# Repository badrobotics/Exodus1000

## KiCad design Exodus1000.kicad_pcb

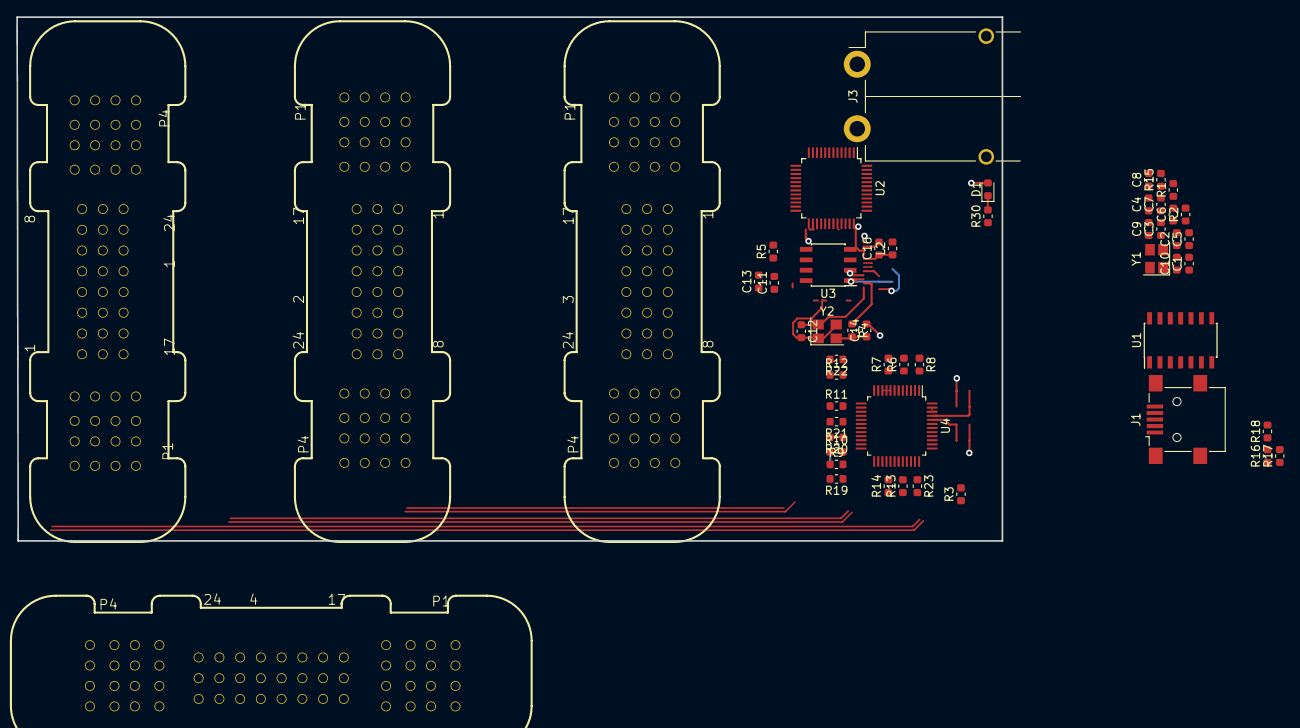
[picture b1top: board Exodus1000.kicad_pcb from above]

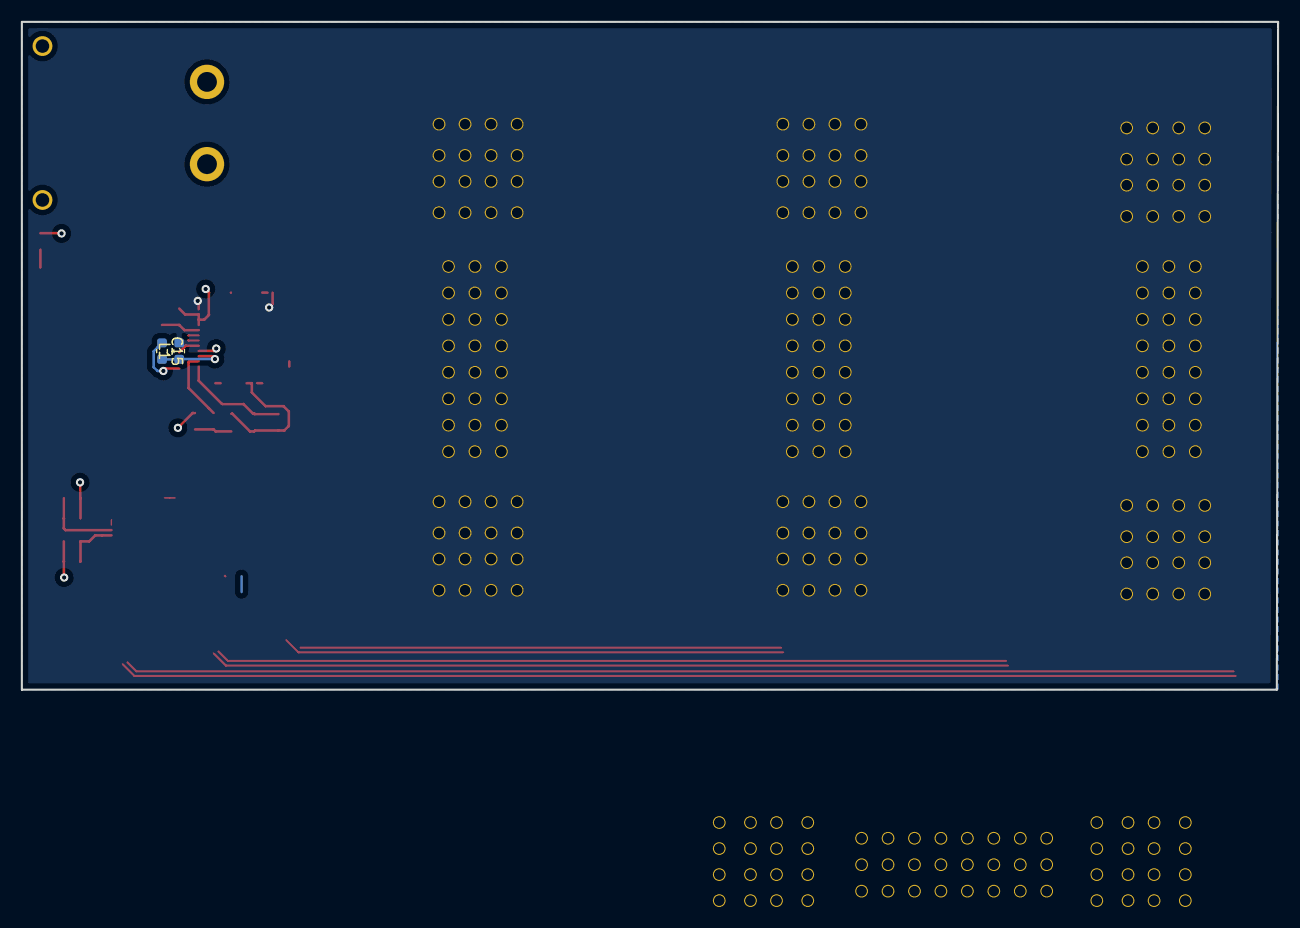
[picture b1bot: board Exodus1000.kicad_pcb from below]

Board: 4 copper layers, 120.7 x 64.1 mm, 55 parts (2 on the bottom side), 54 nets.

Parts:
1, 2, 3, 4: ET60S-02-24-02-X-VP-GP
C1, C2, C3, C4, C5, C6, C7, C8, C9, C10, C11, C12, C13, C14, C15, C16: C_Small; C_0603_1608Metric
D1: LED; LED_0603_1608Metric
J1: USB_B_Mini; USB_Mini-B_Lumberg_2486_01_Horizontal
J3: Conn_01x02; Anderson_PP15_1x2_RightAngle
L1, L2: Ferrite_Bead_Small; L_0603_1608Metric
R1, R2, R3, R4, R5, R6, R7, R8, R9, R10, R11, R12, R13, R14, R15, R16, R17, R18, R19, R20, R21, R22, R23, R30: R_Small; R_0603_1608Metric
U1: 74LS125; SOIC-14_3.9x8.7mm_P1.27mm
U2: tusb2077a; TQFP-48_7x7mm_P0.5mm
U3: 93LCxxB; SOIC-8_3.9x4.9mm_P1.27mm
U4: FT232H; LQFP-48_7x7mm_P0.5mm
Y1: Crystal_GND24; Crystal_SMD_SeikoEpson_FA238-4Pin_3.2x2.5mm
Y2: Crystal_GND24; Crystal_SMD_3225-4Pin_3.2x2.5mm

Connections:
+1V8: C11.1, U4.38
+3V3: 1.P4-1, 1.P4-2, 1.P4-3, 1.P4-4, 1.P4-5, 1.P4-6, 1.P4-7, 1.P4-8, 2.P4-1, 2.P4-2, 2.P4-3, 2.P4-4, 2.P4-5, 2.P4-6, 2.P4-7, 2.P4-8, 3.P4-1, 3.P4-2, 3.P4-3, 3.P4-4, 3.P4-5, 3.P4-6, 3.P4-7, 3.P4-8, 4.P4-1, 4.P4-2, 4.P4-3, 4.P4-4, 4.P4-5, 4.P4-6, 4.P4-7, 4.P4-8, L1.2, L2.2, R18.2, U1.14, U2.8, U2.9, U2.10, U2.46, U2.47, U3.8, U4.12, U4.24, U4.39, U4.40, U4.46
+5V: 1.P3-1, 1.P3-2, 1.P3-3, 1.P3-4, 1.P3-5, 1.P3-6, 1.P3-7, 1.P3-8, 2.P3-1, 2.P3-2, 2.P3-3, 2.P3-4, 2.P3-5, 2.P3-6, 2.P3-7, 2.P3-8, 3.P3-1, 3.P3-2, 3.P3-3, 3.P3-4, 3.P3-5, 3.P3-6, 3.P3-7, 3.P3-8, 4.P3-1, 4.P3-2, 4.P3-3, 4.P3-4, 4.P3-5, 4.P3-6, 4.P3-7, 4.P3-8
+BATT: 1.P2-1, 1.P2-2, 1.P2-3, 1.P2-4, 1.P2-5, 1.P2-6, 1.P2-7, 1.P2-8, 2.P2-1, 2.P2-2, 2.P2-3, 2.P2-4, 2.P2-5, 2.P2-6, 2.P2-7, 2.P2-8, 3.P2-1, 3.P2-2, 3.P2-3, 3.P2-4, 3.P2-5, 3.P2-6, 3.P2-7, 3.P2-8, 4.P2-1, 4.P2-2, 4.P2-3, 4.P2-4, 4.P2-5, 4.P2-6, 4.P2-7, 4.P2-8, D1.2, J3.1
/BOARD_SENSE_1: 3.10, R22.1, U1.1
/BOARD_SENSE_2: 4.10, R23.1, U1.4
/BOARD_SENSE_3: 2.10, R21.1, U1.10
/BOARD_SENSE_4: 1.10, R20.1, U1.13
/D0_N: 3.1, C2.1, R2.2
/D0_P: 3.2, C1.1, R1.2
/D1_N: 4.1, R7.1, R13.2
/D1_P: 4.2, R6.1, R12.2
/D3_N: 1.1, R5.1, R11.2
/D3_P: 1.2, R4.1, R10.2
/D4_N: R9.1, R15.2
/D4_P: R8.1, R14.2
/JTAG_TCK: 1.6, 2.6, 3.6, 4.6, U4.13
/JTAG_TDI: 1.5, U1.11, U4.14
/JTAG_TDO: 3.4, U1.2, U4.15
/JTAG_TDO_1: 3.5, 4.4, U1.3, U1.5
/JTAG_TDO_2: 2.4, 4.5, U1.6, U1.9
/JTAG_TDO_3: 1.4, 2.5, U1.8, U1.12
/JTAG_TMS: 1.3, 2.3, 3.3, 4.3, U4.16
/sheet5CBA03CA/DM0: R2.1, U2.4
/sheet5CBA03CA/DM1: C8.1, R7.2, U2.13
/sheet5CBA03CA/DM3: C6.1, R5.2, U2.21
/sheet5CBA03CA/DM4: C10.1, R9.2, U2.26
/sheet5CBA03CA/DP0: R1.1, R3.2, U2.3
/sheet5CBA03CA/DP1: C7.1, R6.2, U2.14
/sheet5CBA03CA/DP3: C5.1, R4.2, U2.22
/sheet5CBA03CA/DP4: C9.1, R8.2, U2.27
/sheet5CBA03CB/D+: J1.3, U4.7
/sheet5CBA03CB/D-: J1.2, U4.6
/sheet5CBA03CB/OSC0: R17.1, U4.2
/sheet5CBA03CB/OSC0_R: C14.1, R17.2, Y2.2
/sheet5CBA03CB/OSC1: C12.1, U4.1, Y2.4
/~ENABLE: 1.8, 2.8, 3.8, 4.8
/~INHIBIT: 1.16, 2.16, 3.16, 4.16
/~JTAG_TRST: 1.7, 2.7, 3.7, 4.7, U4.17
/~SYSRESET: 1.11, 2.11, 3.11, 4.11, U2.6
GND: 1.P1-1, 1.P1-2, 1.P1-3, 1.P1-4, 1.P1-5, 1.P1-6, 1.P1-7, 1.P1-8, 2.P1-1, 2.P1-2, 2.P1-3, 2.P1-4, 2.P1-5, 2.P1-6, 2.P1-7, 2.P1-8, 3.P1-1, 3.P1-2, 3.P1-3, 3.P1-4, 3.P1-5, 3.P1-6, 3.P1-7, 3.P1-8, 4.P1-1, 4.P1-2, 4.P1-3, 4.P1-4, 4.P1-5, 4.P1-6, 4.P1-7, 4.P1-8, C1.2, C2.2, C3.1, C4.1, C5.2, C6.2, C7.2, C8.2, C9.2, C10.2, C11.2, C12.2, C13.2, C14.2, C15.1, C16.2, J1.5, J1.6, J3.2, R10.1, R11.1, R12.1, R13.1, R14.1, R15.1, R19.2, R20.2, R21.2, R22.2, R23.2, R30.1, U1.7, U2.5, U2.43, U2.48, U3.5, U4.4, U4.9, U4.10, U4.11, U4.22, U4.23, U4.35, U4.36, U4.41, U4.42, U4.47, U4.48, Y1.1, Y1.3, Y2.1, Y2.3
unnamed: C3.2, U2.45, Y1.4
unnamed: C4.2, U2.44, Y1.2
unnamed: C13.1, U4.37
unnamed: C15.2, L1.1, U4.3
unnamed: C16.1, L2.1, U4.8
unnamed: D1.1, R30.2
unnamed: R3.1, U2.2
unnamed: R16.1, U3.3, U4.43
unnamed: R16.2, U3.4
unnamed: R18.1, U4.34
unnamed: R19.1, U4.5
unnamed: U3.1, U4.45
unnamed: U3.2, U4.44

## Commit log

2019-03-10 added some more stuff
2019-03-10 layout stuff
2019-03-16 usb hub and sdram selected.
2019-03-16 cleaning up the usb hub schematic.
2019-03-21 adding gitignore
2019-03-21 schematics for expansion slots and memory
2019-03-22 fixing up the jtag connections. Should be good now
2019-03-22 updated schematic pdf
2019-03-28 almost done with draft 1 of layout
2019-03-29 finished the ram ic routing
2019-04-06 layout done sans connector. It's pretty big. Likely going to need to tear some of this up.
2019-04-17 some layout
2019-05-05 this is just a mess. but I think the schematic is basically right still.
2019-06-26 picking this back up. Removing old unused schematic sheets.
2019-06-26 Create LICENSE
